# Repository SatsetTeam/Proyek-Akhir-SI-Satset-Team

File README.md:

An automatic syringe pump is a device used to inject drugs or liquids automatically. This tool consists of a stepper motor, screw ball mechanism, and syringe. This tool is used to facilitate the injection process, as well as increase accuracy and safety.

simulation link using wokwi: https://wokwi.com/projects/384253886937036801

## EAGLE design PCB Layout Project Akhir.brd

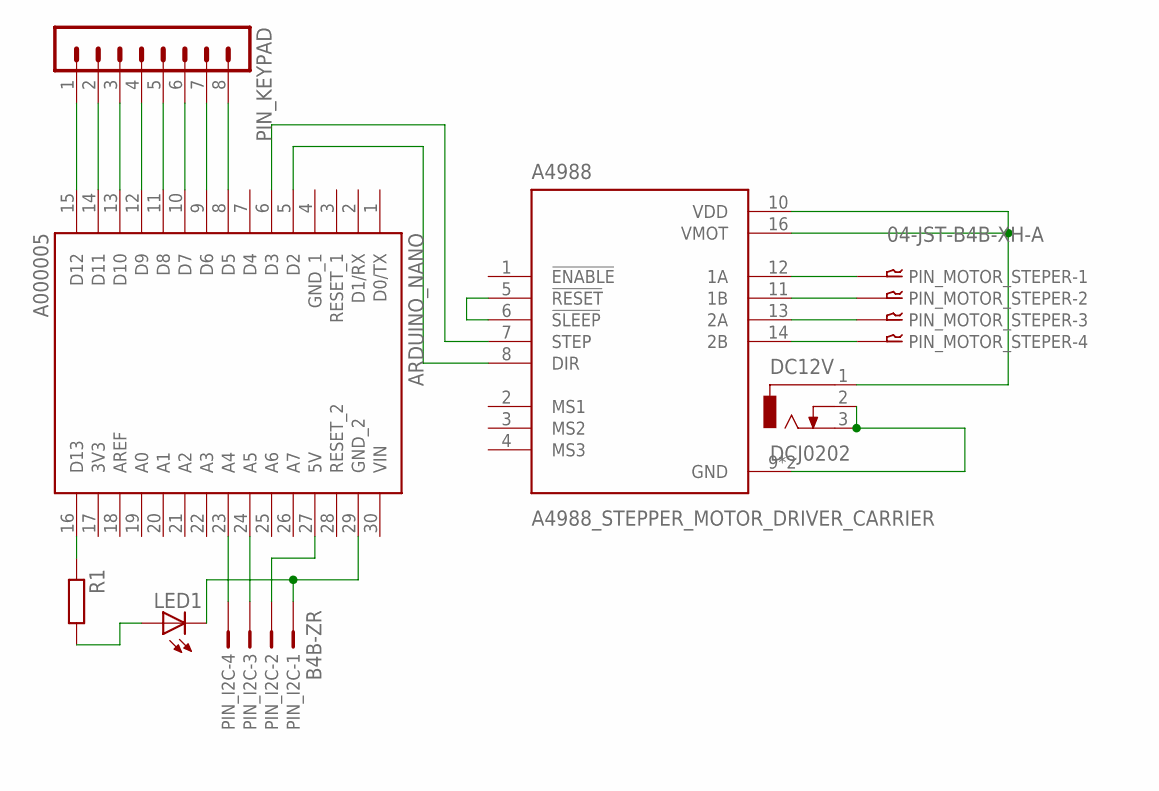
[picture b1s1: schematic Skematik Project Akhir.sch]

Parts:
A4988: A4988_STEPPER_MOTOR_DRIVER_CARRIER; MODULE_A4988_STEPPER_MOTOR_DRIVER_CARRIER
ARDUINO_NANO: A000005; MODULE_A000005
DC12V: DCJ0202
LED1: LED3MM
PIN_I2C: B4B-ZR
PIN_KEYPAD: MA08-1
PIN_MOTOR_STEPER: 04-JST-B4B-XH-A; B4B-XH
R1: R-EU_0207/10; 0207/10

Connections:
3V3: ARDUINO_NANO.17 (3V3)
GND_1: ARDUINO_NANO.4 (GND_1)
unnamed: ARDUINO_NANO.23 (A4), PIN_I2C.4
unnamed: ARDUINO_NANO.24 (A5), PIN_I2C.3
unnamed: ARDUINO_NANO.15 (D12), PIN_KEYPAD.1
unnamed: A4988.12 (1A), PIN_MOTOR_STEPER.P$1
unnamed: ARDUINO_NANO.14 (D11), PIN_KEYPAD.2
unnamed: ARDUINO_NANO.13 (D10), PIN_KEYPAD.3
unnamed: A4988.8 (DIR), ARDUINO_NANO.5 (D2)
unnamed: A4988.7 (STEP), ARDUINO_NANO.6 (D3)
unnamed: ARDUINO_NANO.12 (D9), PIN_KEYPAD.4
unnamed: ARDUINO_NANO.11 (D8), PIN_KEYPAD.5
unnamed: ARDUINO_NANO.10 (D7), PIN_KEYPAD.6
unnamed: ARDUINO_NANO.9 (D6), PIN_KEYPAD.7
unnamed: ARDUINO_NANO.8 (D5), PIN_KEYPAD.8
unnamed: ARDUINO_NANO.16 (D13), R1.1
unnamed: LED1.A, R1.2
unnamed: A4988.11 (1B), PIN_MOTOR_STEPER.P$2
unnamed: A4988.13 (2A), PIN_MOTOR_STEPER.P$3
unnamed: A4988.14 (2B), PIN_MOTOR_STEPER.P$4
unnamed: A4988.5 (!RESET), A4988.6 (!SLEEP)
unnamed: A4988.10 (VDD), A4988.16 (VMOT), DC12V.1
unnamed: A4988.9 (GND), A4988.15 (GND), DC12V.2, DC12V.3
unnamed: ARDUINO_NANO.29 (GND_2), LED1.K (C), PIN_I2C.1
unnamed: ARDUINO_NANO.27 (5V), PIN_I2C.2
VIN: ARDUINO_NANO.30 (VIN)

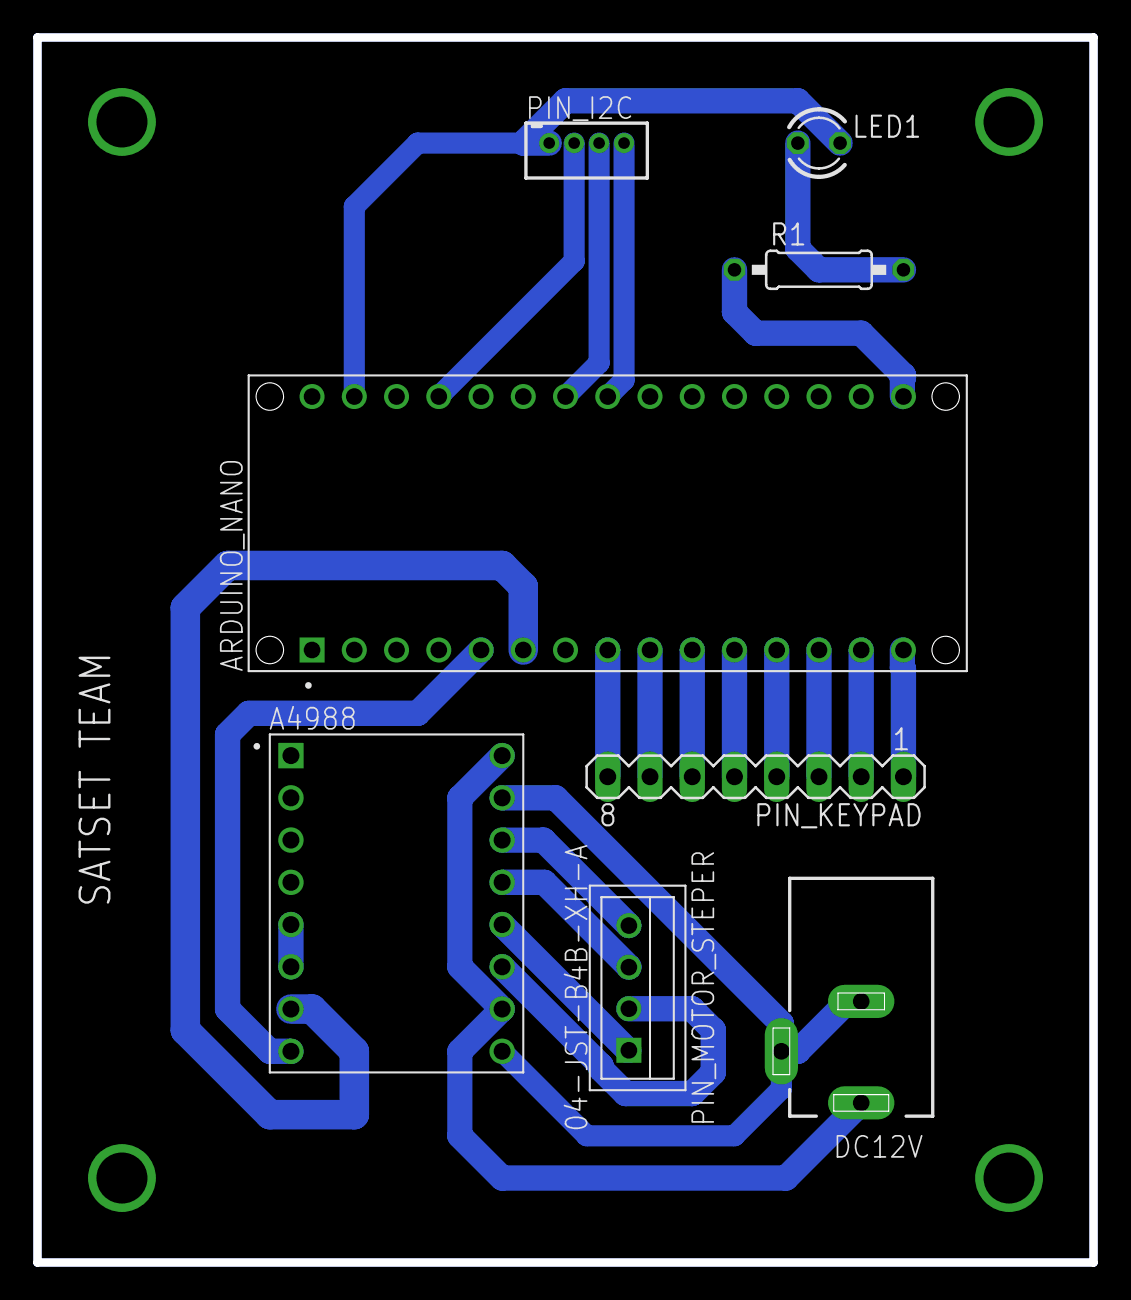
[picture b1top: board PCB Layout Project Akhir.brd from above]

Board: 2 copper layers, 63.5 x 73.7 mm, 8 parts (0 on the bottom side), 23 nets.

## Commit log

2023-12-29 README.md
